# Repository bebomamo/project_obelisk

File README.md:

# Project Overview
Project Obelisk aimed to recreate and enhance the traditional key tag unlocking systems widely used for business security. Our approach replaces the physical key tag with a "custom key" powered by image recognition via artificial intelligence. The "custom key" can be any object that can be uniquely recognized, such as the back of your phone, a rubber duck, or even an apple. The system allows users to dynamically train and store custom keys, which are then used to activate a connected device, such as a servo motor. In our prototype, this servo motor simulates a door lock mechanism, showcasing the concept's functionality.

# About this Project
This project was developed over the course of 10 weeks for the Advanced Digital Systems Lab (ECE395) at UIUC. It involved the creation of a hardware-based system, where my partner and I individually or collaboratively explored the complexities of embedded systems, hardware design, and artificial intelligence. Our journey was marked by numerous challenges that required extensive research, documentation reading, and hands-on troubleshooting, pushing our knowledge and skills in electrical and embedded systems design to new limits.

# Project Obelisk
Project Obelisk is the main undertaking, designed as an all-in-one solution that integrates image processing, AI for object recognition, and a control loop to manage the servo motor and LED indicators. This system seamlessly ties together hardware and software components, allowing for dynamic key recognition and an output signal to trigger external devices.

# Project Obelisk Arduino / Raspberry Pi
The Arduino/Raspberry Pi subproject was designed as a testing environment for simpler systems and to verify our concept before moving to low-level C implementation. This step involved experimenting with synchronization signals, image array padding, and baud rate requirements for camera debugging. Using the Arduino/Raspberry Pi setup allowed us to handle some of the image processing off the primary microcontroller, providing valuable insights into data flow, timing, and system behavior.

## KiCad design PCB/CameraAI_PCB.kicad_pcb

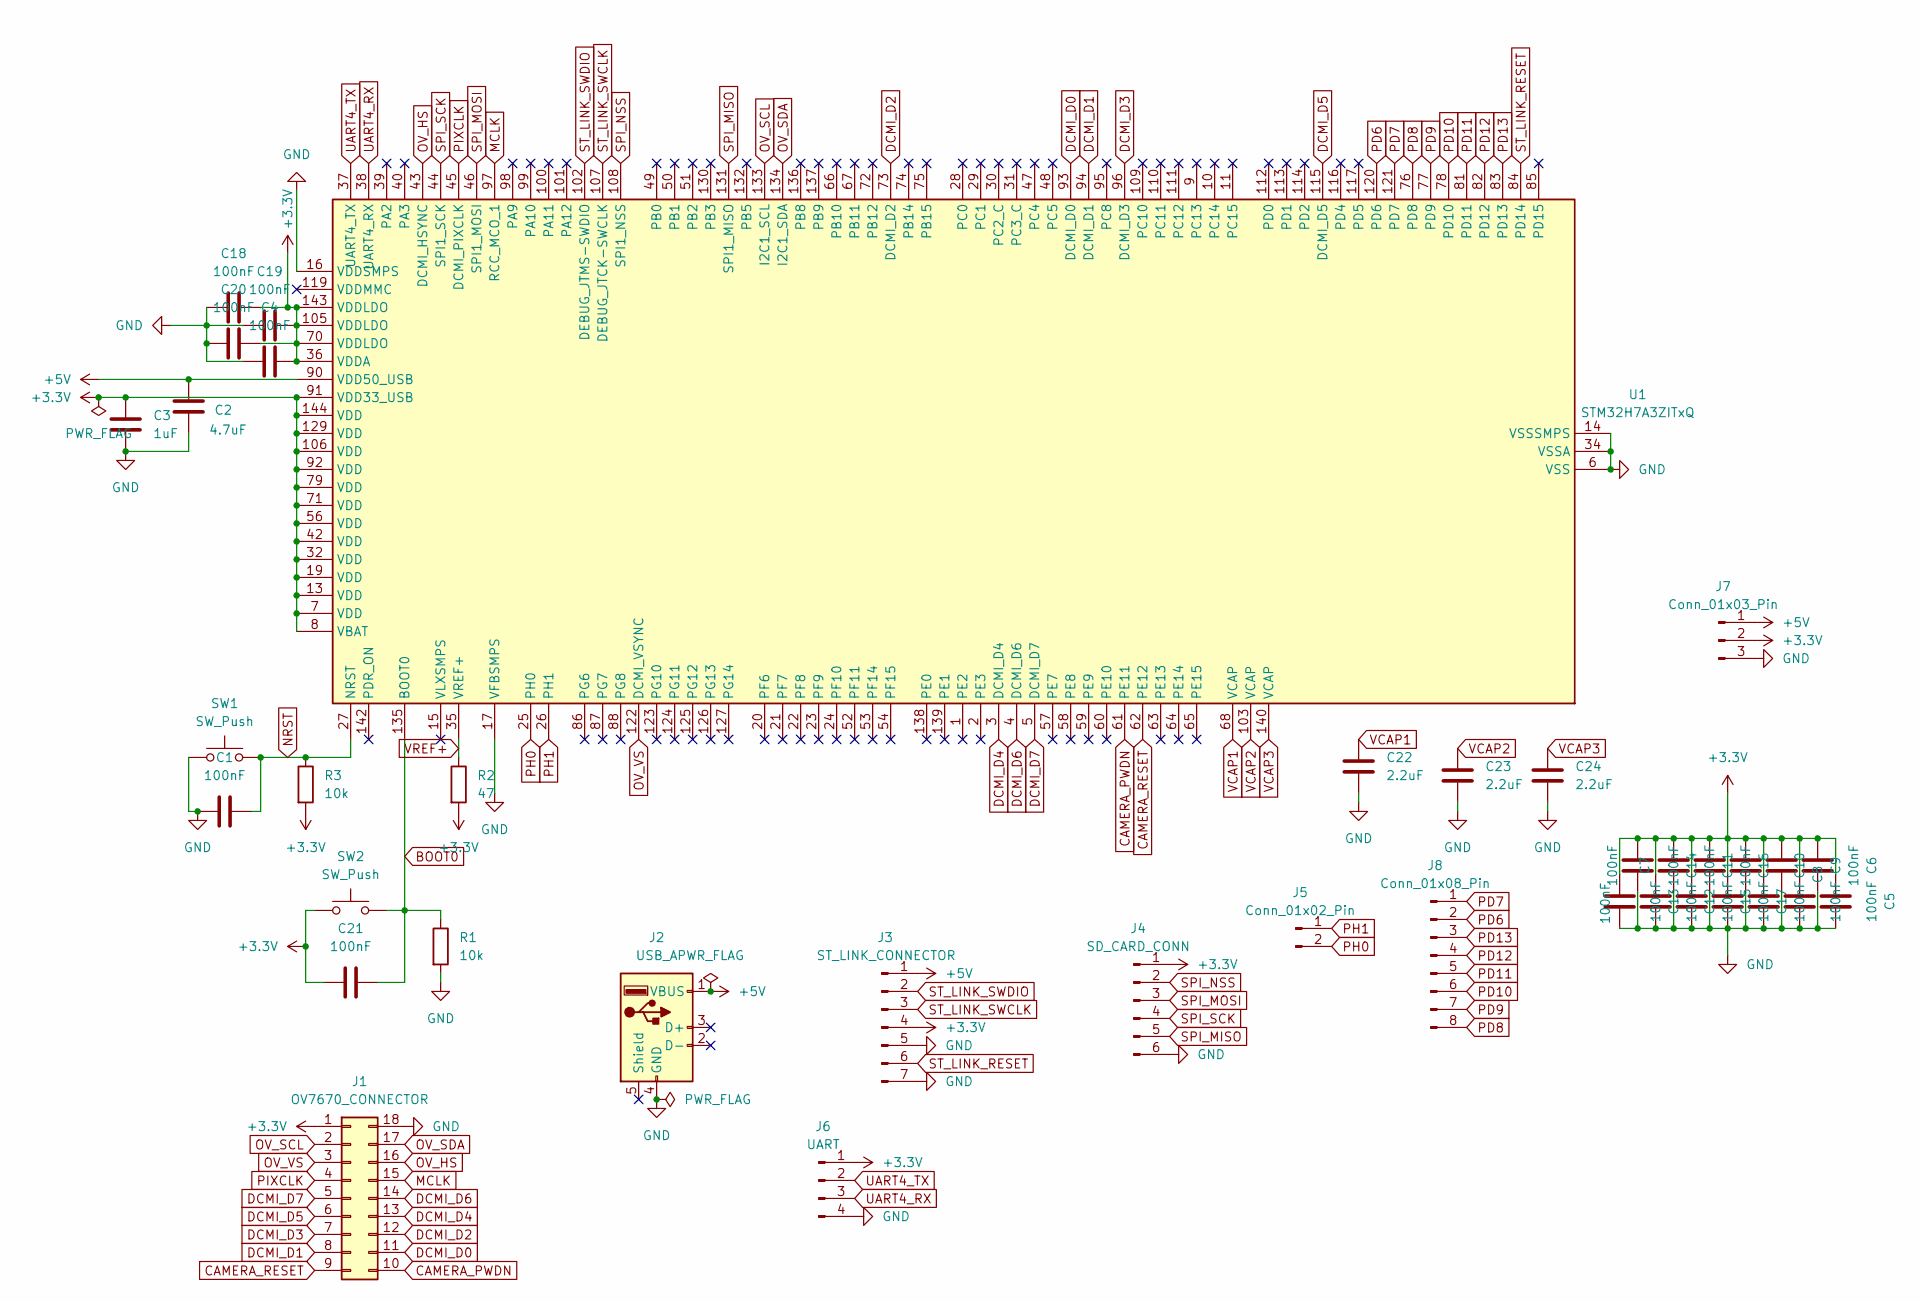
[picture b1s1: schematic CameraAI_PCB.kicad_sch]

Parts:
C1, C4, C5, C6, C7, C8, C9, C10, C11, C12, C13, C14, C15, C16, C17, C18, C19, C20, C21: 100nF; C_0805_2012Metric_Pad1.18x1.45mm_HandSolder
C2: 4.7uF; C_0805_2012Metric_Pad1.18x1.45mm_HandSolder
C3: 1uF; C_0805_2012Metric_Pad1.18x1.45mm_HandSolder
C22, C23, C24: 2.2uF; C_0805_2012Metric_Pad1.18x1.45mm_HandSolder
J1: OV7670_CONNECTOR; PinHeader_2x09_P2.54mm_Horizontal
J2: USB_A; USB3_A_Molex_48393-001
J3: ST_LINK_CONNECTOR; PinHeader_1x07_P2.54mm_Vertical
J4: SD_CARD_CONN; PinHeader_1x06_P2.54mm_Vertical
J5: Conn_01x02_Pin; PinHeader_1x02_P2.54mm_Vertical
J6: UART; PinHeader_1x04_P2.54mm_Vertical
J7: Conn_01x03_Pin; PinHeader_1x03_P2.54mm_Vertical
J8: Conn_01x08_Pin; PinHeader_1x08_P2.54mm_Vertical
R1, R3: 10k; R_0805_2012Metric_Pad1.20x1.40mm_HandSolder
R2: 47; R_0805_2012Metric_Pad1.20x1.40mm_HandSolder
SW1, SW2: SW_Push; Nidec_Copal_SH-7010A
U1: STM32H7A3ZITxQ; LQFP-144_20x20mm_P0.5mm

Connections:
+3.3V: C3.1, C4.1, C5.2, C6.2, C7.2, C8.2, C9.2, C10.2, C11.2, C12.2, C13.2, C14.2, C15.2, C16.2, C17.2, C18.1, C19.1, C20.1, C21.1, J1.1, J3.4, J4.1, J6.1, J7.2, R2.2, R3.2, SW2.1, U1.7 (VDD), U1.8 (VBAT), U1.13 (VDD), U1.19 (VDD), U1.32 (VDD), U1.36 (VDDA), U1.42 (VDD), U1.56 (VDD), U1.70 (VDDLDO), U1.71 (VDD), U1.79 (VDD), U1.91 (VDD33_USB), U1.92 (VDD), U1.105 (VDDLDO), U1.106 (VDD), U1.129 (VDD), U1.143 (VDDLDO), U1.144 (VDD)
+5V: C2.2, J2.1 (VBUS), J3.1, J7.1, U1.90 (VDD50_USB)
BOOT0: C21.2, R1.1, SW2.2, U1.135 (BOOT0)
CAMERA_PWDN: J1.10, U1.61 (PE11)
CAMERA_RESET: J1.9, U1.62 (PE12)
DCMI_D0: J1.11, U1.93 (DCMI_D0)
DCMI_D1: J1.8, U1.94 (DCMI_D1)
DCMI_D2: J1.12, U1.73 (DCMI_D2)
DCMI_D3: J1.7, U1.96 (DCMI_D3)
DCMI_D4: J1.13, U1.3 (DCMI_D4)
DCMI_D5: J1.6, U1.115 (DCMI_D5)
DCMI_D6: J1.14, U1.4 (DCMI_D6)
DCMI_D7: J1.5, U1.5 (DCMI_D7)
GND: C1.1, C2.1, C3.2, C4.2, C5.1, C6.1, C7.1, C8.1, C9.1, C10.1, C11.1, C12.1, C13.1, C14.1, C15.1, C16.1, C17.1, C18.2, C19.2, C20.2, C22.1, C23.1, C24.1, J1.18, J2.4 (GND), J3.5, J3.7, J4.6, J6.4, J7.3, R1.2, SW1.1, U1.6 (VSS), U1.12 (VSS), U1.14 (VSSSMPS), U1.16 (VDDSMPS), U1.17 (VFBSMPS), U1.18 (VSS), U1.33 (VSS), U1.34 (VSSA), U1.41 (VSS), U1.55 (VSS), U1.69 (VSS), U1.80 (VSS), U1.89 (VSS), U1.104 (VSS), U1.118 (VSS), U1.128 (VSS), U1.141 (VSS)
MCLK: J1.15, U1.97 (RCC_MCO_1)
NRST: C1.2, R3.1, SW1.2, U1.27 (NRST)
OV_HS: J1.16, U1.43 (DCMI_HSYNC)
OV_SCL: J1.2, U1.133 (I2C1_SCL)
OV_SDA: J1.17, U1.134 (I2C1_SDA)
OV_VS: J1.3, U1.122 (DCMI_VSYNC)
PD6: J8.2, U1.120 (PD6)
PD7: J8.1, U1.121 (PD7)
PD8: J8.8, U1.76 (PD8)
PD9: J8.7, U1.77 (PD9)
PD10: J8.6, U1.78 (PD10)
PD11: J8.5, U1.81 (PD11)
PD12: J8.4, U1.82 (PD12)
PD13: J8.3, U1.83 (PD13)
PH0: J5.2, U1.25 (PH0)
PH1: J5.1, U1.26 (PH1)
PIXCLK: J1.4, U1.45 (DCMI_PIXCLK)
SPI_MISO: J4.5, U1.131 (SPI1_MISO)
SPI_MOSI: J4.3, U1.46 (SPI1_MOSI)
SPI_NSS: J4.2, U1.108 (SPI1_NSS)
SPI_SCK: J4.4, U1.44 (SPI1_SCK)
ST_LINK_RESET: J3.6, U1.84 (PD14)
ST_LINK_SWCLK: J3.3, U1.107 (DEBUG_JTCK-SWCLK)
ST_LINK_SWDIO: J3.2, U1.102 (DEBUG_JTMS-SWDIO)
UART4_RX: J6.3, U1.38 (UART4_RX)
UART4_TX: J6.2, U1.37 (UART4_TX)
VCAP1: C22.2, U1.68 (VCAP)
VCAP2: C23.2, U1.103 (VCAP)
VCAP3: C24.2, U1.140 (VCAP)
VREF+: R2.1, U1.35 (VREF+)

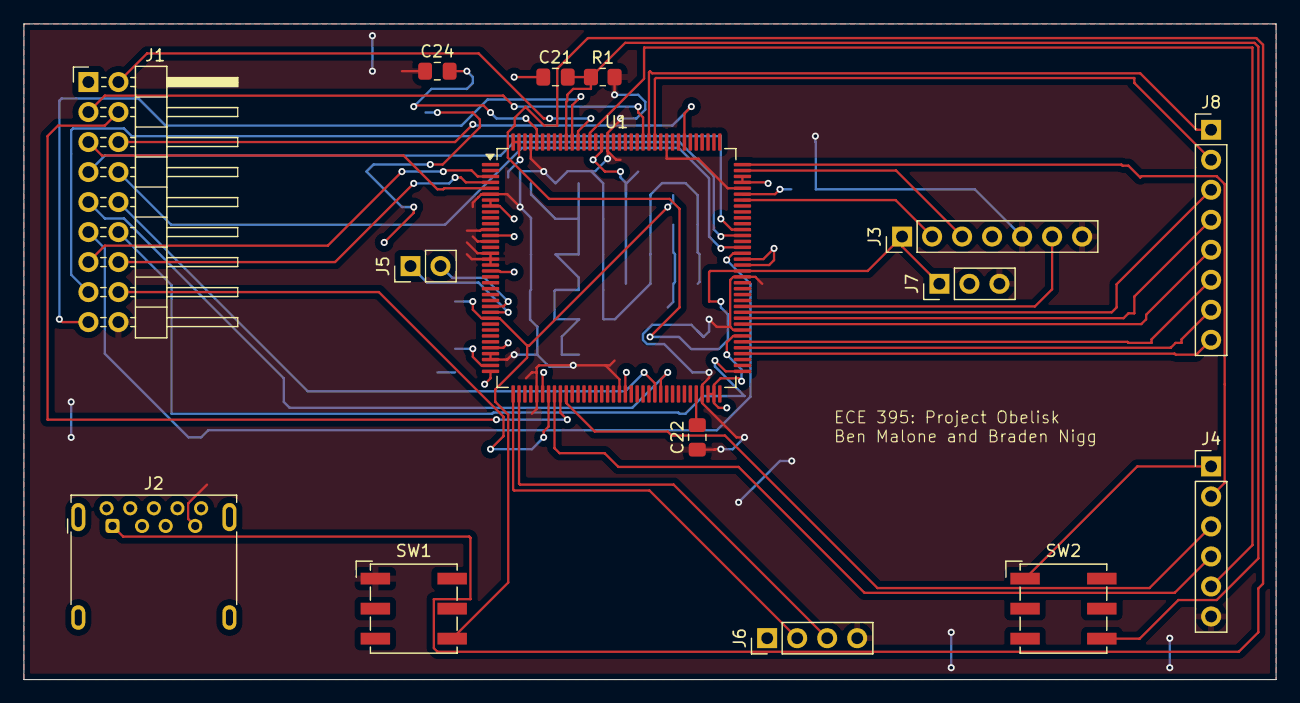
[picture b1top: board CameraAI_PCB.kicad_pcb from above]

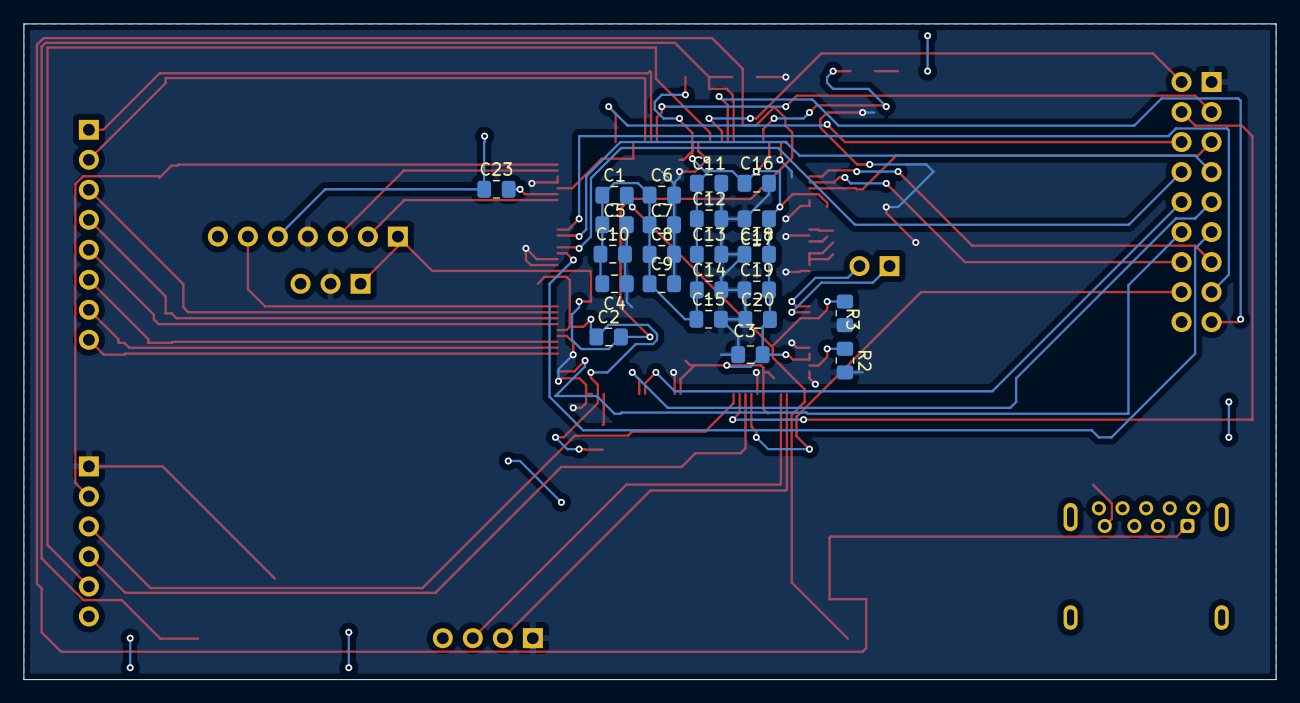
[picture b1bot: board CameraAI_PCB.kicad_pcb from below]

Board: 2 copper layers, 106.0 x 55.5 mm, 38 parts (23 on the bottom side), 44 nets.

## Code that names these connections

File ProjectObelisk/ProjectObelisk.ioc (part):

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Mcu.Name=STM32H7A3Z(G-I)TxQ
Mcu.Package=LQFP144
Mcu.UserName=STM32H7A3ZITxQ
PA0.Mode=Asynchronous
PA0.Signal=UART4_TX
PA1.Mode=Asynchronous
PA1.Signal=UART4_RX
PA13.Mode=Serial_Wire
PA13.Signal=DEBUG_JTMS-SWDIO
PA14.Mode=Serial_Wire
PA14.Signal=DEBUG_JTCK-SWCLK
PA15.Mode=NSS_Signal_Hard_Input
PA15.Signal=SPI1_NSS
PA4.GPIOParameters=GPIO_Speed,GPIO_PuPd
PA4.GPIO_PuPd=GPIO_PULLDOWN
PA4.GPIO_Speed=GPIO_SPEED_FREQ_VERY_HIGH
PA4.Mode=Slave_8_bits_External_Synchro
PA4.Signal=DCMI_HSYNC
PA5.Mode=Full_Duplex_Master
PA5.Signal=SPI1_SCK
PA6.GPIOParameters=GPIO_Speed,GPIO_PuPd
PA6.GPIO_PuPd=GPIO_PULLDOWN
PA6.GPIO_Speed=GPIO_SPEED_FREQ_VERY_HIGH
PA6.Mode=Slave_8_bits_External_Synchro
PA6.Signal=DCMI_PIXCLK
PA7.Mode=Full_Duplex_Master
PA7.Signal=SPI1_MOSI
PA8.GPIOParameters=GPIO_Speed
PA8.GPIO_Speed=GPIO_SPEED_FREQ_VERY_HIGH
PA8.Mode=Clock-out-1
PA8.Signal=RCC_MCO_1
PB13.GPIOParameters=GPIO_Speed,GPIO_PuPd
PB13.GPIO_PuPd=GPIO_PULLDOWN
PB13.GPIO_Speed=GPIO_SPEED_FREQ_VERY_HIGH
PB13.Mode=Slave_8_bits_External_Synchro
PB13.Signal=DCMI_D2
PB4.Mode=Full_Duplex_Master
PB4.Signal=SPI1_MISO
PB6.Mode=I2C
PB6.Signal=I2C1_SCL
PB7.Mode=I2C
PB7.Signal=I2C1_SDA
PC6.GPIOParameters=GPIO_Speed,GPIO_PuPd
PC6.GPIO_PuPd=GPIO_PULLDOWN
PC6.GPIO_Speed=GPIO_SPEED_FREQ_VERY_HIGH
PC6.Mode=Slave_8_bits_External_Synchro
PC6.Signal=DCMI_D0
PC7.GPIOParameters=GPIO_Speed,GPIO_PuPd
PC7.GPIO_PuPd=GPIO_PULLDOWN
PC7.GPIO_Speed=GPIO_SPEED_FREQ_VERY_HIGH
PC7.Mode=Slave_8_bits_External_Synchro
PC7.Signal=DCMI_D1
PC9.GPIOParameters=GPIO_Speed,GPIO_PuPd
PC9.GPIO_PuPd=GPIO_PULLDOWN
PC9.GPIO_Speed=GPIO_SPEED_FREQ_VERY_HIGH
PC9.Mode=Slave_8_bits_External_Synchro
PC9.Signal=DCMI_D3
PD10.GPIOParameters=GPIO_Label
PD10.GPIO_Label=TRAIN_IMG1_BUTTON
PD10.Signal=GPIO_Input
PD11.GPIOParameters=GPIO_Label
PD11.GPIO_Label=TRAIN_IMG2_BUTTON
PD11.Signal=GPIO_Input
PD12.GPIOParameters=GPIO_Label
PD12.GPIO_Label=SERVO_PWM
PD12.Signal=S_TIM4_CH1
PD3.GPIOParameters=GPIO_Speed,GPIO_PuPd
PD3.GPIO_PuPd=GPIO_PULLDOWN
PD3.GPIO_Speed=GPIO_SPEED_FREQ_VERY_HIGH
PD3.Mode=Slave_8_bits_External_Synchro
PD3.Signal=DCMI_D5
PD6.GPIOParameters=GPIO_Label
PD6.GPIO_Label=GREEN_LED
PD6.Signal=GPIO_Output
PD7.GPIOParameters=GPIO_Label
PD7.GPIO_Label=RED_LED
PD7.Signal=GPIO_Output
PD8.GPIOParameters=GPIO_Label
PD8.GPIO_Label=BLUE_LED
PD8.Signal=GPIO_Output
PD9.GPIOParameters=GPIO_Label
PD9.GPIO_Label=DECIDER_BUTTON
PD9.Signal=GPIO_Input
PE11.GPIOParameters=GPIO_Label
PE11.GPIO_Label=CAMERA_PWDN
PE11.Signal=GPIO_Output
PE12.GPIOParameters=GPIO_Label
PE12.GPIO_Label=CAMERA_RESET
PE12.Signal=GPIO_Output
PE4.GPIOParameters=GPIO_Speed,GPIO_PuPd
PE4.GPIO_PuPd=GPIO_PULLDOWN
PE4.GPIO_Speed=GPIO_SPEED_FREQ_VERY_HIGH
PE4.Mode=Slave_8_bits_External_Synchro
PE4.Signal=DCMI_D4
PE5.GPIOParameters=GPIO_Speed,GPIO_PuPd
PE5.GPIO_PuPd=GPIO_PULLDOWN
PE5.GPIO_Speed=GPIO_SPEED_FREQ_VERY_HIGH
PE5.Mode=Slave_8_bits_External_Synchro
PE5.Signal=DCMI_D6
PE6.GPIOParameters=GPIO_Speed,GPIO_PuPd
PE6.GPIO_PuPd=GPIO_PULLDOWN
PE6.GPIO_Speed=GPIO_SPEED_FREQ_VERY_HIGH
PE6.Mode=Slave_8_bits_External_Synchro
PE6.Signal=DCMI_D7
PG9.GPIOParameters=GPIO_Speed,GPIO_PuPd
PG9.GPIO_PuPd=GPIO_PULLDOWN
PG9.GPIO_Speed=GPIO_SPEED_FREQ_VERY_HIGH
PG9.Mode=Slave_8_bits_External_Synchro
PG9.Signal=DCMI_VSYNC
RCC.SYSCLKFreq_VALUE=168000000
RCC.SYSCLKSource=RCC_SYSCLKSOURCE_PLLCLK
board=custom

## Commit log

2025-03-20 Dumping most of the project
2025-03-20 adding last folder, which was too large
